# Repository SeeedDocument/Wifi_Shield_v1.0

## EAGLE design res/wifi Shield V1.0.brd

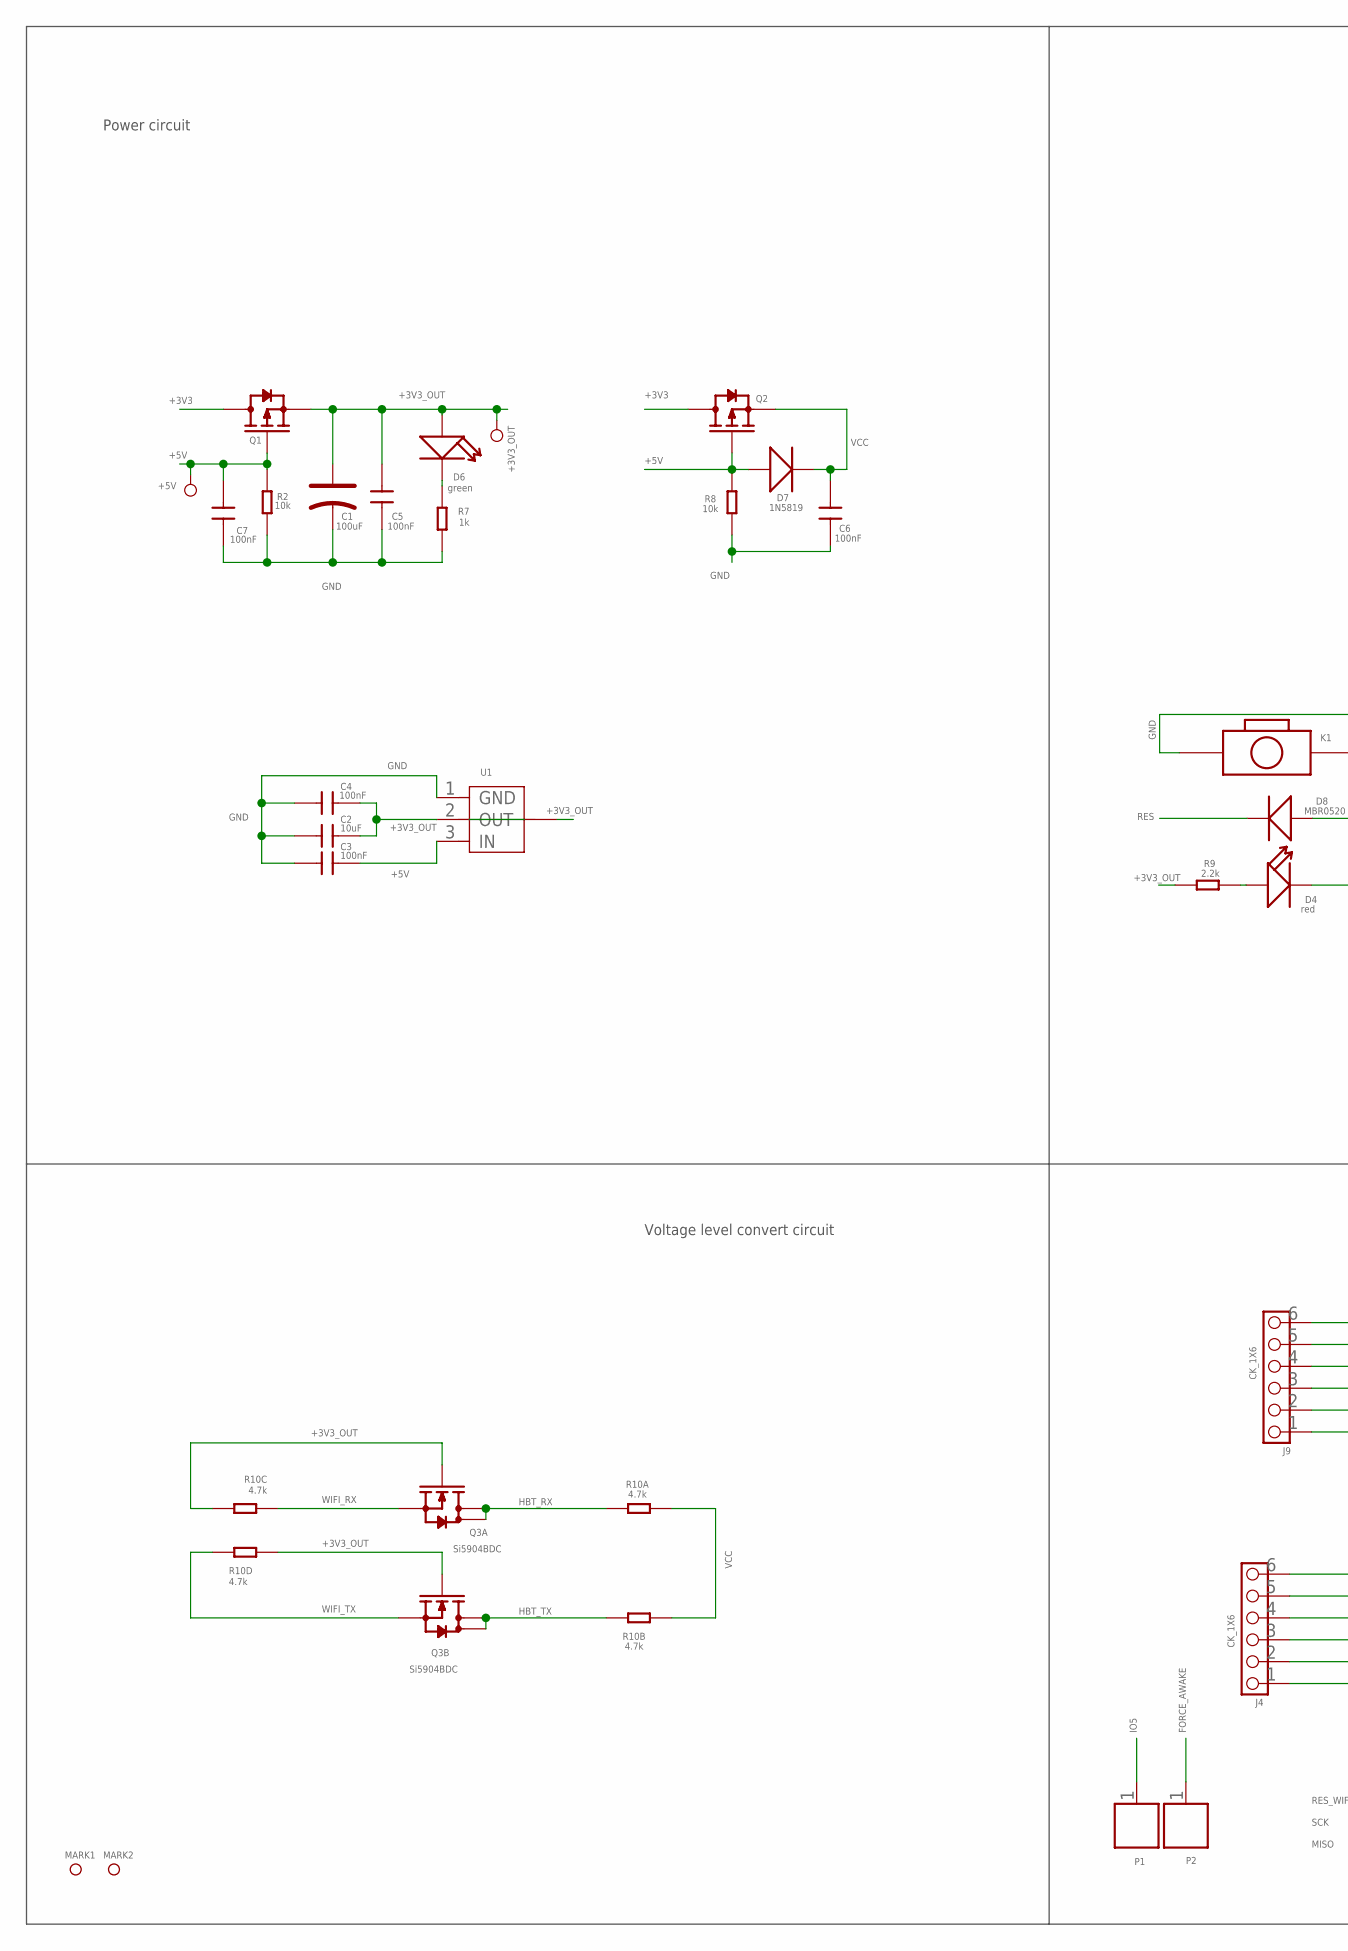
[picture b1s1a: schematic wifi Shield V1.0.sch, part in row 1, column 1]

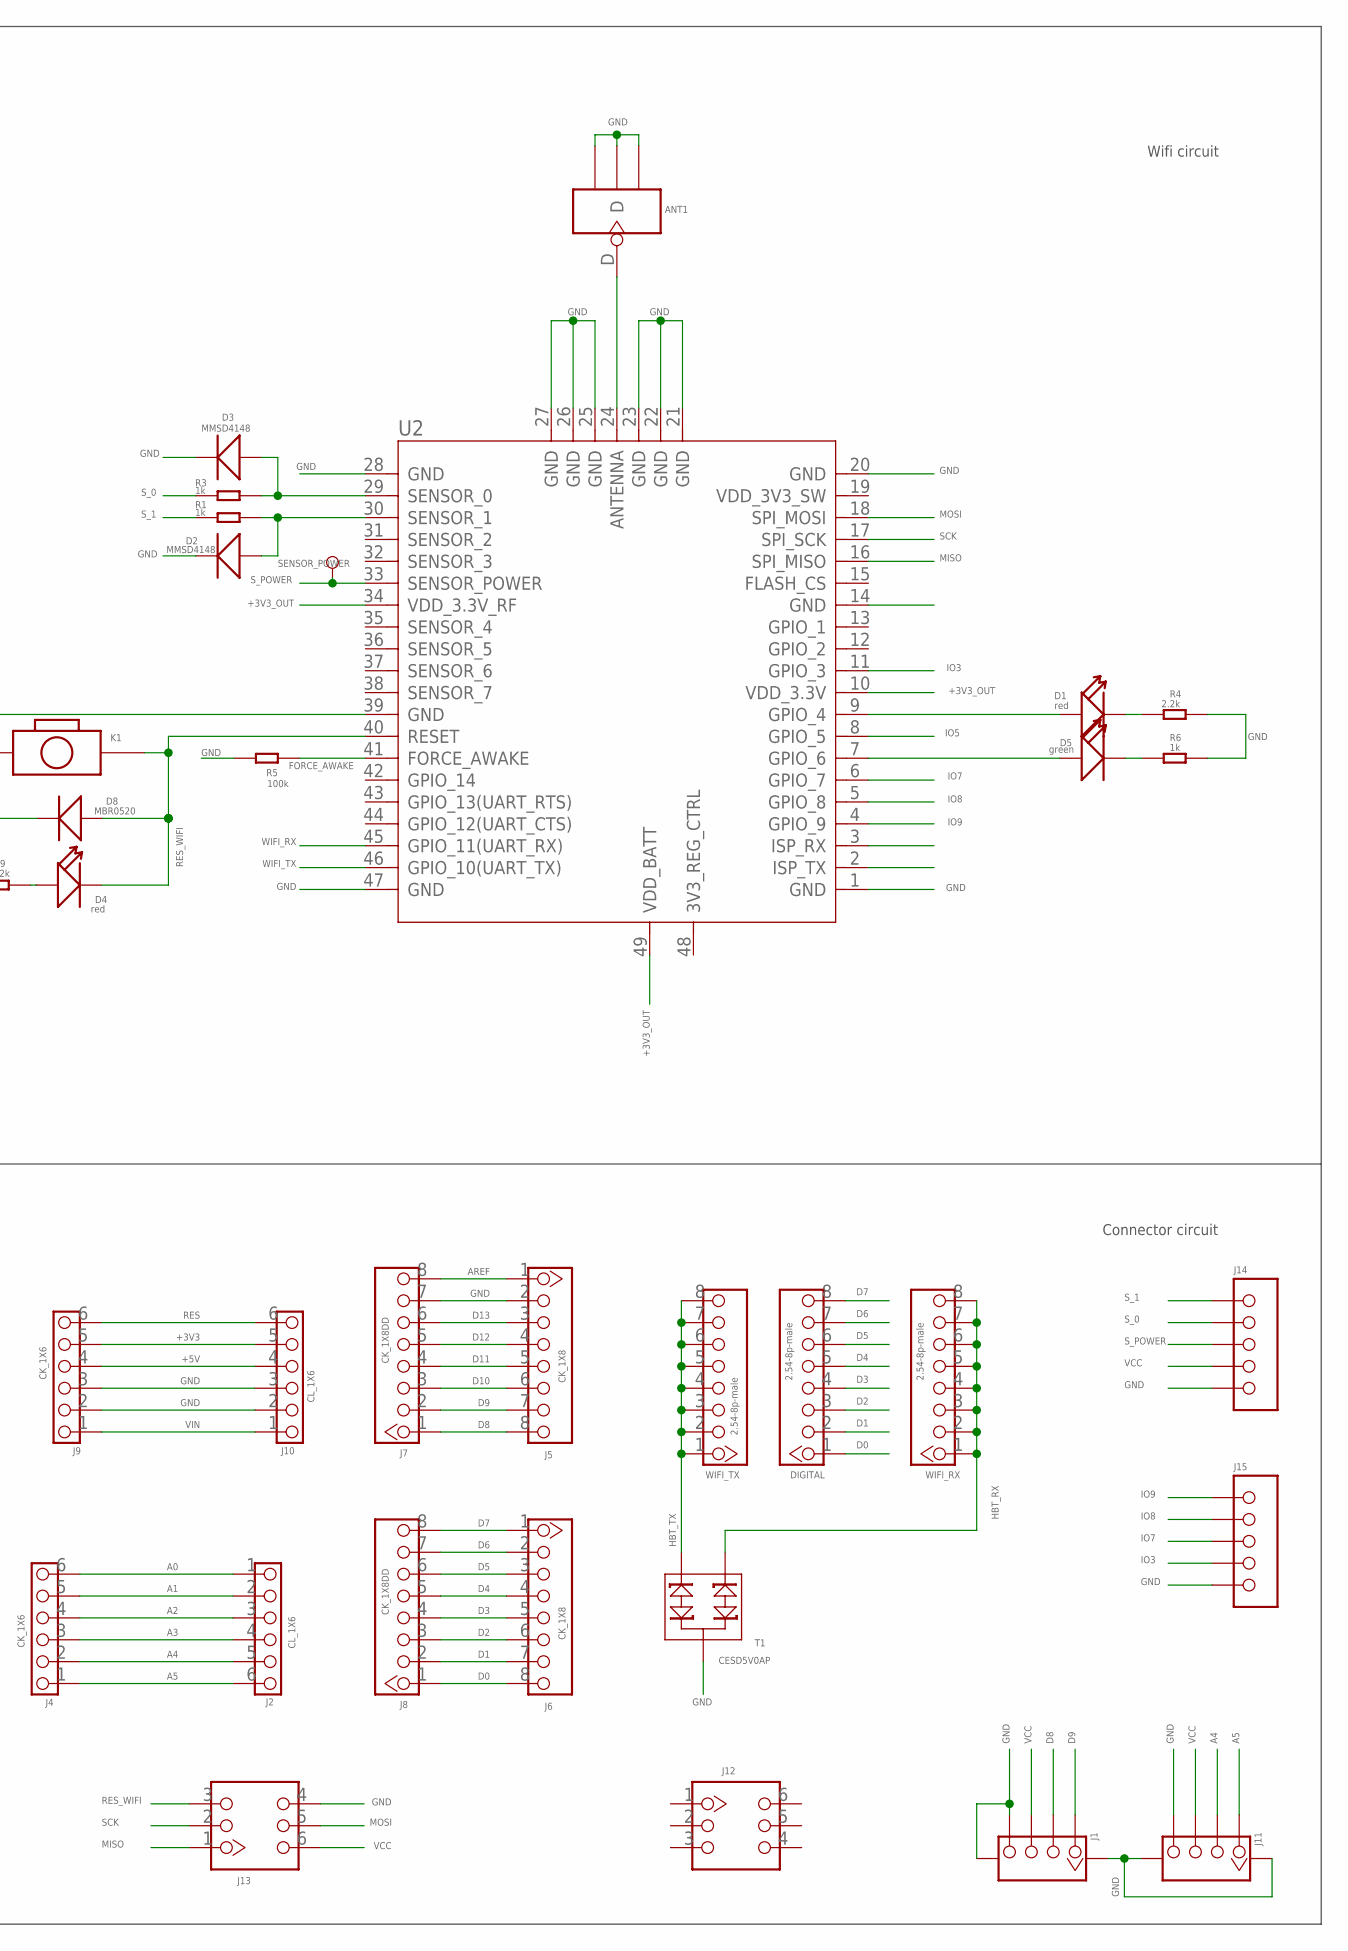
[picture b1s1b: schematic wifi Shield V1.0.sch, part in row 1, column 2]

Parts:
+3V3_OUT, +5V: PAD-TEST-POINT-CIRCLE_SIZE_3030; TP_3535
ANT1: ANTENNA-U-FL; 4P-U-FL
C1: 100uF; AVX-B
C2: 10uF; 0603
C3, C4, C5, C6, C7: 100nF; 0603
D1, D4: red; LED-0603
D2, D3: MMSD4148; SOD123-2.7X1.6
D5, D6: green; LED-0603
D7: 1N5819; D2010
D8: MBR0520; SOD123-2.7X1.6
DIGITAL: 2.54-8p-male; 8P-2.54
J1, J11: TWIG-4P-2.0-SMD-FEMALE-REINFORCE'90D'; 4P-SMD-2.0-90D
J2, J10: CL_1X6; 6P-2.54-65/35MIL
J4, J9: CK_1X6; 6P-2.54-65/35MIL
J5, J6: CK_1X8; 8P-2.54
J7, J8: CK_1X8DD; 8P-2.54
J12, J13: HEADER-2X3P-2.54; 2X3P-2.54
J14, J15: HEADER-5P-2.54; 5P-2.54
K1: BOTTON-2P-90; 2P-7.62X3.56-90D
MARK1, MARK2: PAD-MARK; ROUND-MARK-0.635
P1, P2: PAD'60/30'; 1P-65/35MIL
Q1, Q2: MOSFET-P'SI2323CDS/SI2305DS<BR>'; SOT23
Q3: Si5904BDC; 1206-8
R1, R3, R6, R7: 1k; 0603
R2, R8: 10k; 0603
R4, R9: 2.2k; 0603
R5: 100k; 0603
R10: 4.7k; R1206-8
SENSOR_POWER: PAD-TEST-POINT-CIRCLE_SIZE_3030; TP_3535
T1: CESD5V0AP; SOT23
U1: LD1117SOT89; SOT89
U2: WIFI-RN-171; 49P-1.27-26.67X17.78
WIFI_RX: 2.54-8p-male; 8P-2.54
WIFI_TX: 2.54-8p-male; 8P-2.54

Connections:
+3V3: J9.5, J10.5, Q1.3 (D), Q2.3 (D)
+3V3_OUT: +3V3_OUT.T, C1.+, C2.2, C4.2, C5.1, D6.+, Q1.2 (S), Q3.2 (G), Q3.4 (G), R9.2, R10.5 (2), R10.6 (2), U1.2 (OUT), U1.4 (TAB), U2.10 (VDD_3.3V), U2.34 (VDD_3.3V_RF), U2.49 (VDD_BATT)
+5V: +5V.T, C3.2, C7.1, D7.+, J9.4, J10.4, Q1.1 (G), Q2.1 (G), R2.1, R8.1, U1.3 (IN)
A0: J2.1, J4.6
A1: J2.2, J4.5
A2: J2.3, J4.4
A3: J2.4, J4.3
A4: J2.5, J4.2, J11.2
A5: J2.6, J4.1, J11.1
AREF: J5.1, J7.8
D0: DIGITAL.1, J6.8, J8.1
D1: DIGITAL.2, J6.7, J8.2
D2: DIGITAL.3, J6.6, J8.3
D3: DIGITAL.4, J6.5, J8.4
D4: DIGITAL.5, J6.4, J8.5
D5: DIGITAL.6, J6.3, J8.6
D6: DIGITAL.7, J6.2, J8.7
D7: DIGITAL.8, J6.1, J8.8
D8: J1.2, J5.8, J7.1
D9: J1.1, J5.7, J7.2
D10: J5.6, J7.3
D11: J5.5, J7.4
D12: J5.4, J7.5
D13: J5.3, J7.6
FORCE_AWAKE: P2.1, R5.1, U2.41 (FORCE_AWAKE)
GND: ANT1.GND1, ANT1.GND2, ANT1.GND3, C1.-, C2.1, C3.1, C4.1, C5.2, C6.2, C7.2, D2.1 (-), D3.1 (-), J1.4, J1.SS1, J1.SS2, J5.2, J7.7, J9.2, J9.3, J10.2, J10.3, J11.4, J11.SS1, J11.SS2, J13.4, J14.5, J15.5, K1.P$2 (2), R2.2, R4.1, R5.2, R6.1, R7.1, R8.2, T1.3, U1.1 (GND), U2.1 (GND), U2.14 (GND), U2.20 (GND), U2.21 (GND), U2.22 (GND), U2.23 (GND), U2.25 (GND), U2.26 (GND), U2.27 (GND), U2.28 (GND), U2.39 (GND), U2.47 (GND)
HBT_RX: Q3.7 (D), Q3.8 (D), R10.1, T1.1, WIFI_RX.1, WIFI_RX.2, WIFI_RX.3, WIFI_RX.4, WIFI_RX.5, WIFI_RX.6, WIFI_RX.7, WIFI_RX.8
HBT_TX: Q3.5 (D), Q3.6 (D), R10.2 (1), T1.2, WIFI_TX.1, WIFI_TX.2, WIFI_TX.3, WIFI_TX.4, WIFI_TX.5, WIFI_TX.6, WIFI_TX.7, WIFI_TX.8
IO3: J15.4, U2.11 (GPIO_3)
IO5: P1.1, U2.8 (GPIO_5)
IO7: J15.3, U2.6 (GPIO_7)
IO8: J15.2, U2.5 (GPIO_8)
IO9: J15.1, U2.4 (GPIO_9)
MISO: J13.1, U2.16 (SPI_MISO)
MOSI: J13.5, U2.18 (SPI_MOSI)
unnamed: D4.+, R9.1
unnamed: D3.2 (+), R3.1, U2.29 (SENSOR_0)
unnamed: D2.2 (+), R1.1, U2.30 (SENSOR_1)
unnamed: D5.+, U2.7 (GPIO_6)
unnamed: ANT1.D, U2.24 (ANTENNA)
unnamed: D1.+, U2.9 (GPIO_4)
unnamed: D5.-, R6.2
unnamed: D1.-, R4.2
unnamed: D6.-, R7.2
RES: D8.1 (-), J9.6, J10.6
RES_WIFI: D4.-, D8.2 (+), J13.3, K1.P$1 (1), U2.40 (RESET)
SCK: J13.2, U2.17 (SPI_SCK)
S_0: J14.2, R3.2
S_1: J14.1, R1.2
S_POWER: J14.3, SENSOR_POWER.T, U2.33 (SENSOR_POWER)
VCC: C6.1, D7.-, J1.3, J11.3, J13.6, J14.4, Q2.2 (S), R10.7 (2), R10.8 (2)
VIN: J9.1, J10.1
WIFI_RX: Q3.1 (S), R10.3 (1), U2.45 (GPIO_11(UART_RX))
WIFI_TX: Q3.3 (S), R10.4 (1), U2.46 (GPIO_10(UART_TX))

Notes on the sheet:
Power circuit
Wifi circuit
Voltage level convert circuit
Connector circuit

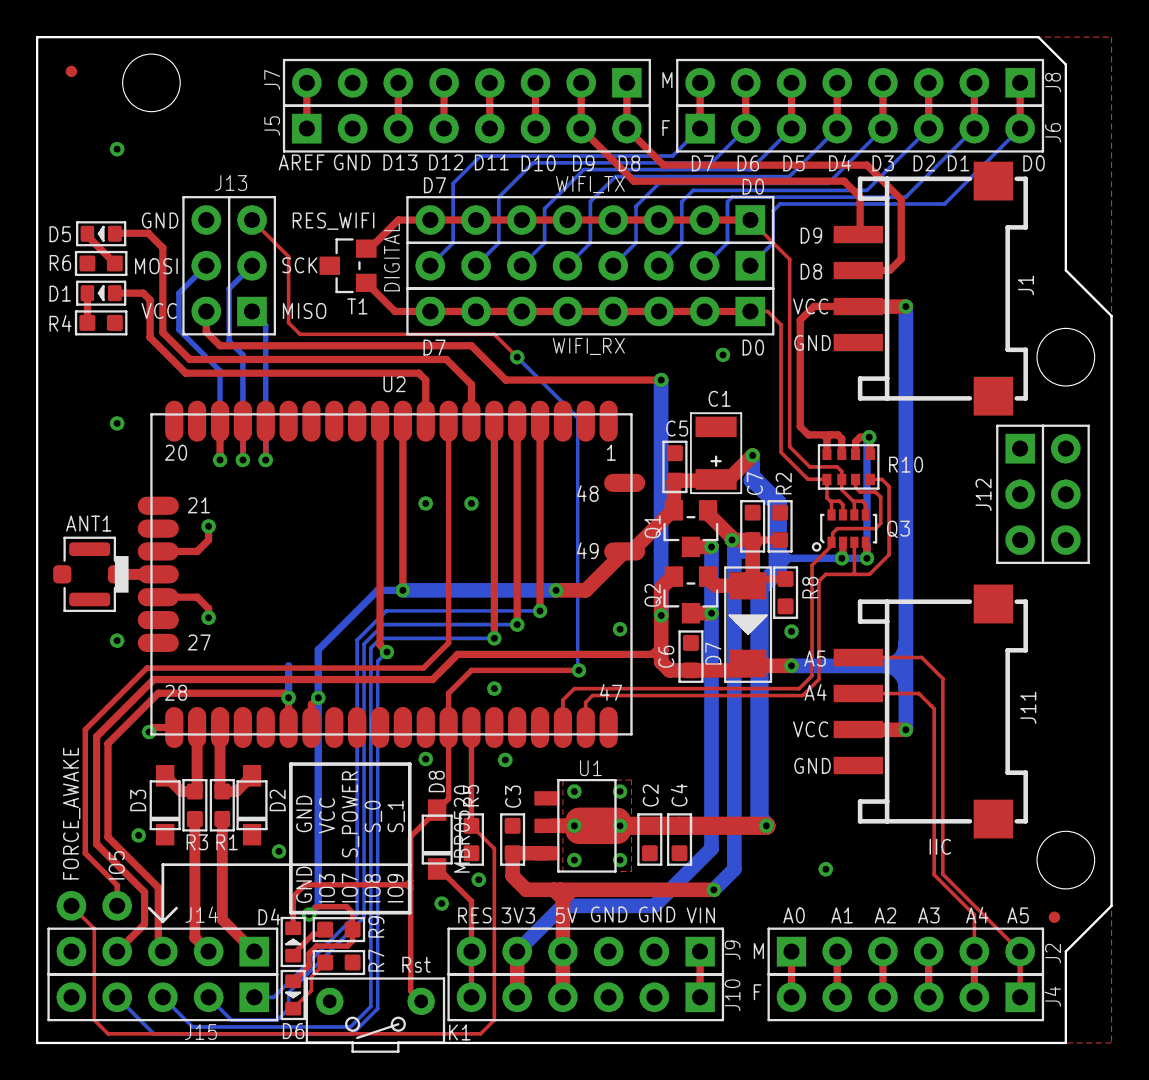
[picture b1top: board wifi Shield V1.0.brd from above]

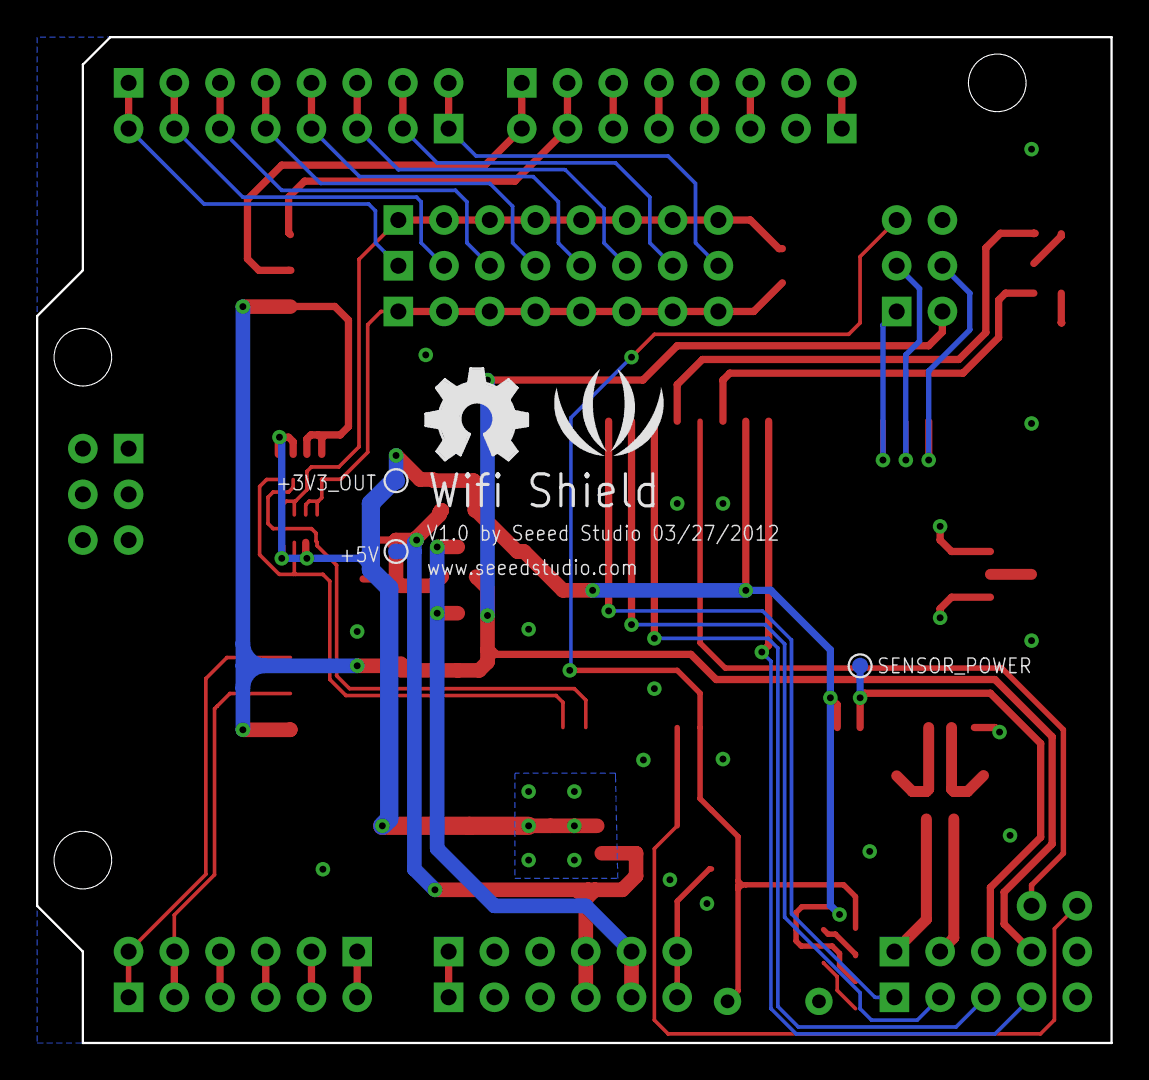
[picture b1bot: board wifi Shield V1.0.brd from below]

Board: 2 copper layers, 59.7 x 55.9 mm, 59 parts (5 on the bottom side), 54 nets.

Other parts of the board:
U$1: OSHW_FILLX200_NOTEXT
U$2: LOGO_SILK

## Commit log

2017-05-24 upgrade
2019-11-06 add
    add
